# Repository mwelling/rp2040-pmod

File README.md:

# rp2040-pmod

Simple RP2040 MCU based PMOD

# Features
* RP2040 MCU
* SPI flash
* USB
* 2x6 PMOD
* Analog header
* LED
* 1 User Button
* Reset and Boot Button
* Debug header

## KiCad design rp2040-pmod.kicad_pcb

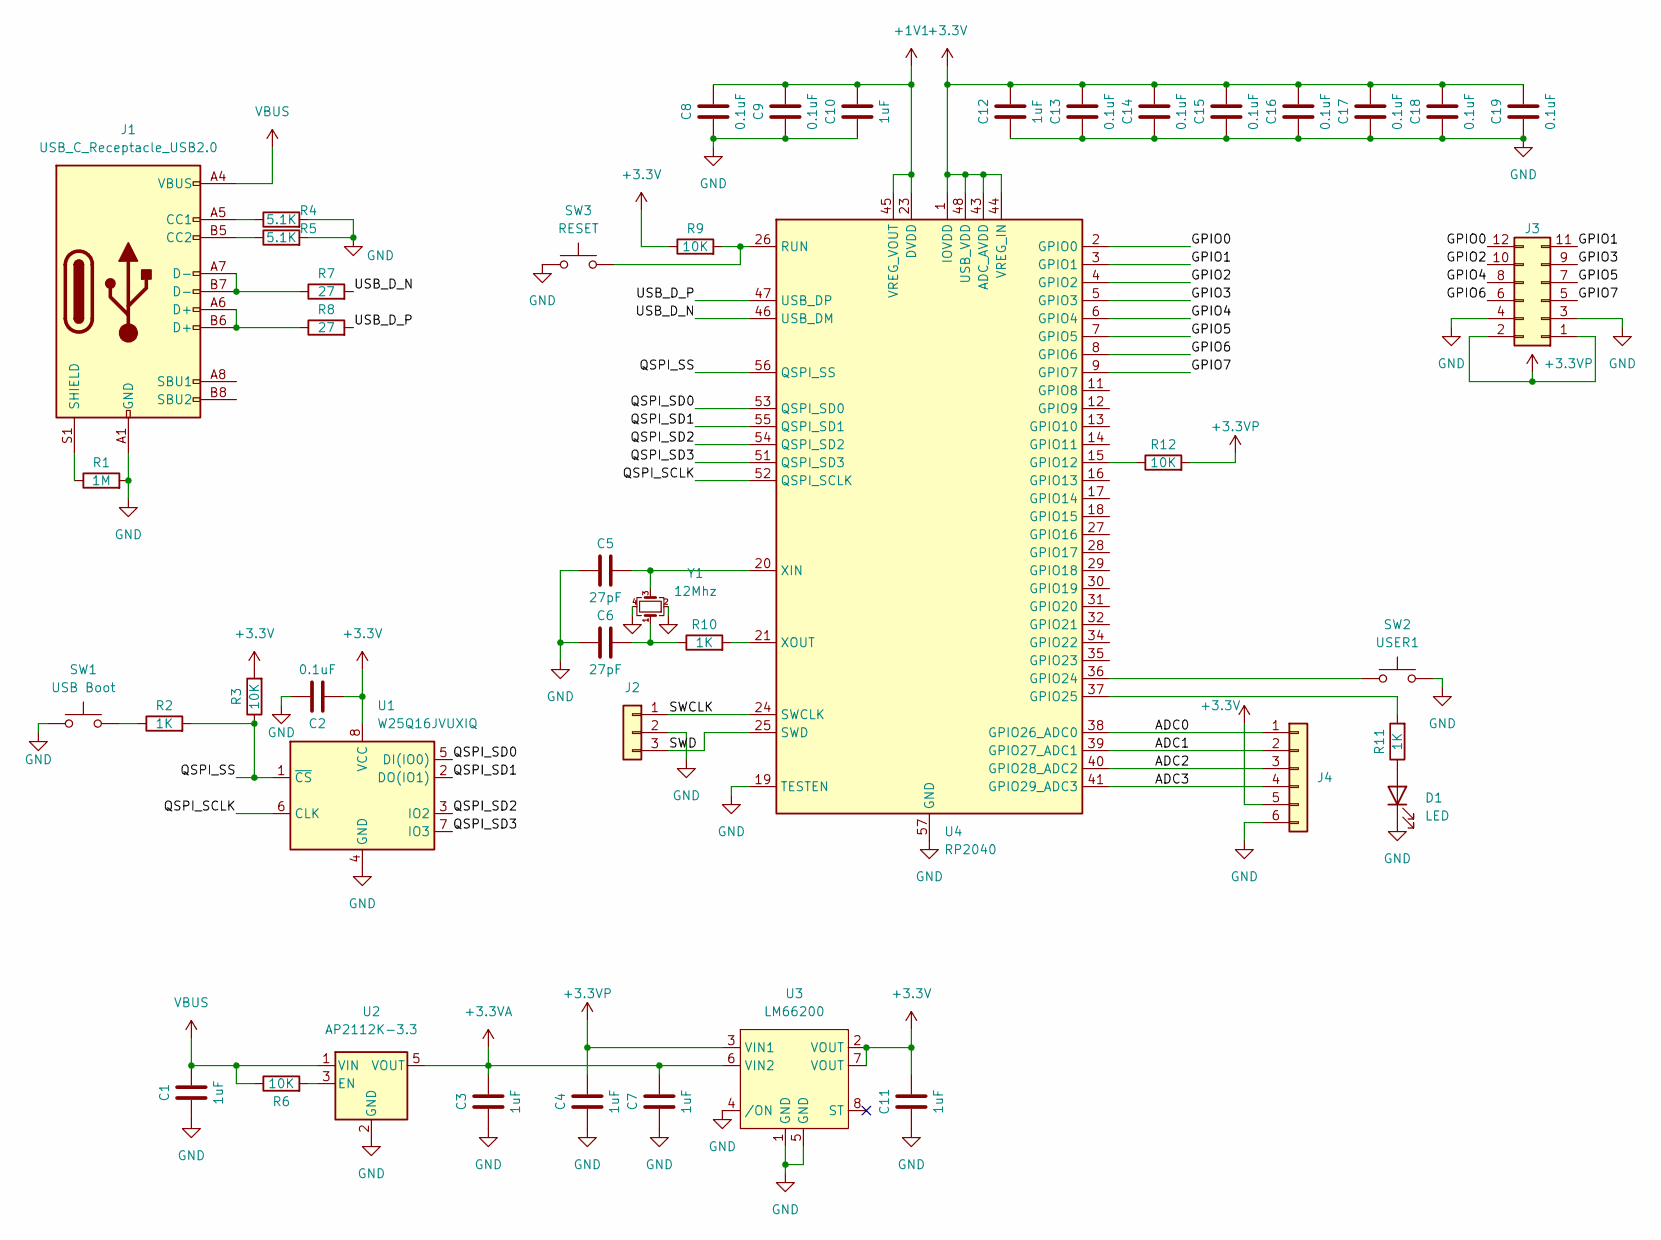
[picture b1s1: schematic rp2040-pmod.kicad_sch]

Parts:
C1, C3, C4, C7, C10, C11, C12: 1uF; C_0402_1005Metric
C2, C8, C9, C13, C14, C15, C16, C17, C18, C19: 0.1uF; C_0402_1005Metric
C5, C6: 27pF; C_0402_1005Metric
D1: LED; LED_0402_1005Metric
J1: USB_C_Receptacle_USB2.0; USB_C_Receptacle_HRO_TYPE-C-31-M-12
J2: Conn_01x03; PinHeader_1x03_P2.54mm_Vertical
J3: Conn_02x06_Odd_Even; PinHeader_2x06_P2.54mm_Horizontal
J4: Conn_01x06; PinHeader_1x06_P2.54mm_Vertical
R1: 1M; R_0402_1005Metric
R2, R10, R11: 1K; R_0402_1005Metric
R3, R6, R9, R12: 10K; R_0402_1005Metric
R4, R5: 5.1K; R_0402_1005Metric
R7, R8: 27; R_0402_1005Metric
SW1: USB Boot; SW_Push_1P1T_NO_Vertical_Wuerth_434133025816
SW2: USER1; SW_Push_1P1T_NO_Vertical_Wuerth_434133025816
SW3: RESET; SW_Push_1P1T_NO_Vertical_Wuerth_434133025816
U1: W25Q16JVUXIQ; USON-8_2x3
U2: AP2112K-3.3; SOT-23-5
U3: LM66200; SOT-5x3
U4: RP2040; QFN-56-1EP_7x7mm_P0.4mm_EP3.2x3.2mm
Y1: 12Mhz; Crystal_SMD_Abracon_ABM8G-4Pin_3.2x2.5mm

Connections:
+1V1: C8.2, C9.2, C10.2, U4.23 (DVDD), U4.45 (VREG_VOUT), U4.50 (DVDD)
+3.3V: C2.1, C11.2, C12.2, C13.2, C14.2, C15.2, C16.2, C17.2, C18.2, C19.2, J4.5, R3.2, R9.1, U1.8 (VCC), U3.2 (VOUT), U3.7 (VOUT), U4.1 (IOVDD), U4.10 (IOVDD), U4.22 (IOVDD), U4.33 (IOVDD), U4.42 (IOVDD), U4.43 (ADC_AVDD), U4.44 (VREG_IN), U4.48 (USB_VDD), U4.49 (IOVDD)
+3.3VA: C3.2, C7.2, U2.5 (VOUT), U3.6 (VIN2)
+3.3VP: C4.2, J3.1, J3.2, R12.2, U3.3 (VIN1)
/ADC0: J4.1, U4.38 (GPIO26_ADC0)
/ADC1: J4.2, U4.39 (GPIO27_ADC1)
/ADC2: J4.3, U4.40 (GPIO28_ADC2)
/ADC3: J4.4, U4.41 (GPIO29_ADC3)
/GPIO0: J3.12, U4.2 (GPIO0)
/GPIO1: J3.11, U4.3 (GPIO1)
/GPIO2: J3.10, U4.4 (GPIO2)
/GPIO3: J3.9, U4.5 (GPIO3)
/GPIO4: J3.8, U4.6 (GPIO4)
/GPIO5: J3.7, U4.7 (GPIO5)
/GPIO6: J3.6, U4.8 (GPIO6)
/GPIO7: J3.5, U4.9 (GPIO7)
/QSPI_SCLK: U1.6 (CLK), U4.52 (QSPI_SCLK)
/QSPI_SD0: U1.5 (DI(IO0)), U4.53 (QSPI_SD0)
/QSPI_SD1: U1.2 (DO(IO1)), U4.55 (QSPI_SD1)
/QSPI_SD2: U1.3 (IO2), U4.54 (QSPI_SD2)
/QSPI_SD3: U1.7 (IO3), U4.51 (QSPI_SD3)
/QSPI_SS: R2.2, R3.1, U1.1 (~CS), U4.56 (QSPI_SS)
/SWCLK: J2.1, U4.24 (SWCLK)
/SWD: J2.3, U4.25 (SWD)
/USB_D_N: R7.2, U4.46 (USB_DM)
/USB_D_P: R8.2, U4.47 (USB_DP)
GND: C1.1, C2.2, C3.1, C4.1, C5.1, C6.1, C7.1, C8.1, C9.1, C10.1, C11.1, C12.1, C13.1, C14.1, C15.1, C16.1, C17.1, C18.1, C19.1, D1.1 (K), J1.A1 (GND), J1.A12 (GND), J1.B1 (GND), J1.B12 (GND), J2.2, J3.3, J3.4, J4.6, R1.2, R4.2, R5.2, SW1.1, SW2.2, SW3.1, U1.4 (GND), U2.2 (GND), U3.1 (GND), U3.4 (/ON), U3.5 (GND), U4.19 (TESTEN), U4.57 (GND), Y1.2, Y1.4
unnamed: C5.2, U4.20 (XIN), Y1.3
unnamed: C6.2, R10.1, Y1.1
unnamed: D1.2 (A), R11.1
unnamed: J1.A5 (CC1), R4.1
unnamed: J1.A6 (D+), J1.B6 (D+), R8.1
unnamed: J1.A7 (D-), J1.B7 (D-), R7.1
unnamed: J1.B5 (CC2), R5.1
unnamed: J1.S1 (SHIELD), R1.1
unnamed: R2.1, SW1.2
unnamed: R6.2, U2.3 (EN)
unnamed: R9.2, SW3.2, U4.26 (RUN)
unnamed: R10.2, U4.21 (XOUT)
unnamed: R11.2, U4.37 (GPIO25)
unnamed: SW2.1, U4.36 (GPIO24)
unnamed: R12.1, U4.15 (GPIO12)
VBUS: C1.2, J1.A4 (VBUS), J1.A9 (VBUS), J1.B4 (VBUS), J1.B9 (VBUS), R6.1, U2.1 (VIN)

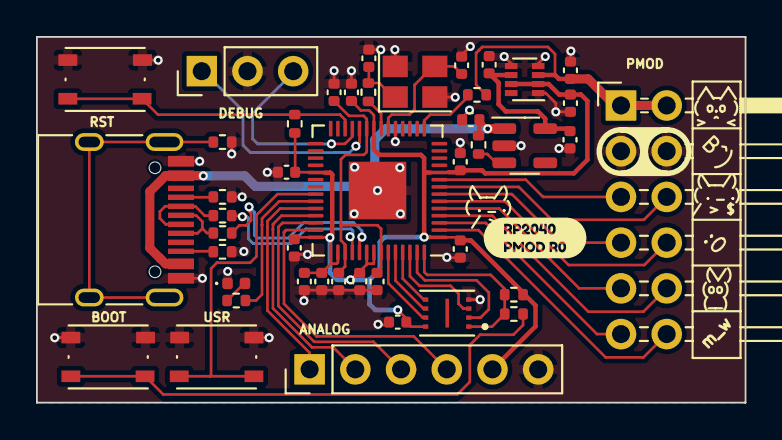
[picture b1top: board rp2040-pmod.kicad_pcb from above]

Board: 2 copper layers, 39.4 x 20.3 mm, 46 parts (1 on the bottom side), 43 nets.

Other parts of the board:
kibuzzard-6385637E, kibuzzard-6385637E#2: G***; kibuzzard-6385637E

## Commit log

2022-11-01 Initial commit for peer review
2022-11-01 Routed in 2 layers
2022-11-02 Switch to .1" debug header
    Also add some silkscreen labels on the bottom.
2022-11-02 Fix some new DRCs
2022-11-15 Update LM66200 footprint
    The footprint used was the wrong pitch and width. :(
    New footprint is close enough to the datasheet to actually work. :)
2022-11-15 Switch flash, add ADC header, add PMOD power detection
    USON pattern swiped from emeb's library.
    https://github.com/emeb/KiCad_Libs
2022-11-30 Silkscreen updates
2023-03-06 Add BOM and schematic PDF
2023-03-06 Create LICENSE
2023-03-06 Add image of the board
2024-11-29 Update to Kicad 8
